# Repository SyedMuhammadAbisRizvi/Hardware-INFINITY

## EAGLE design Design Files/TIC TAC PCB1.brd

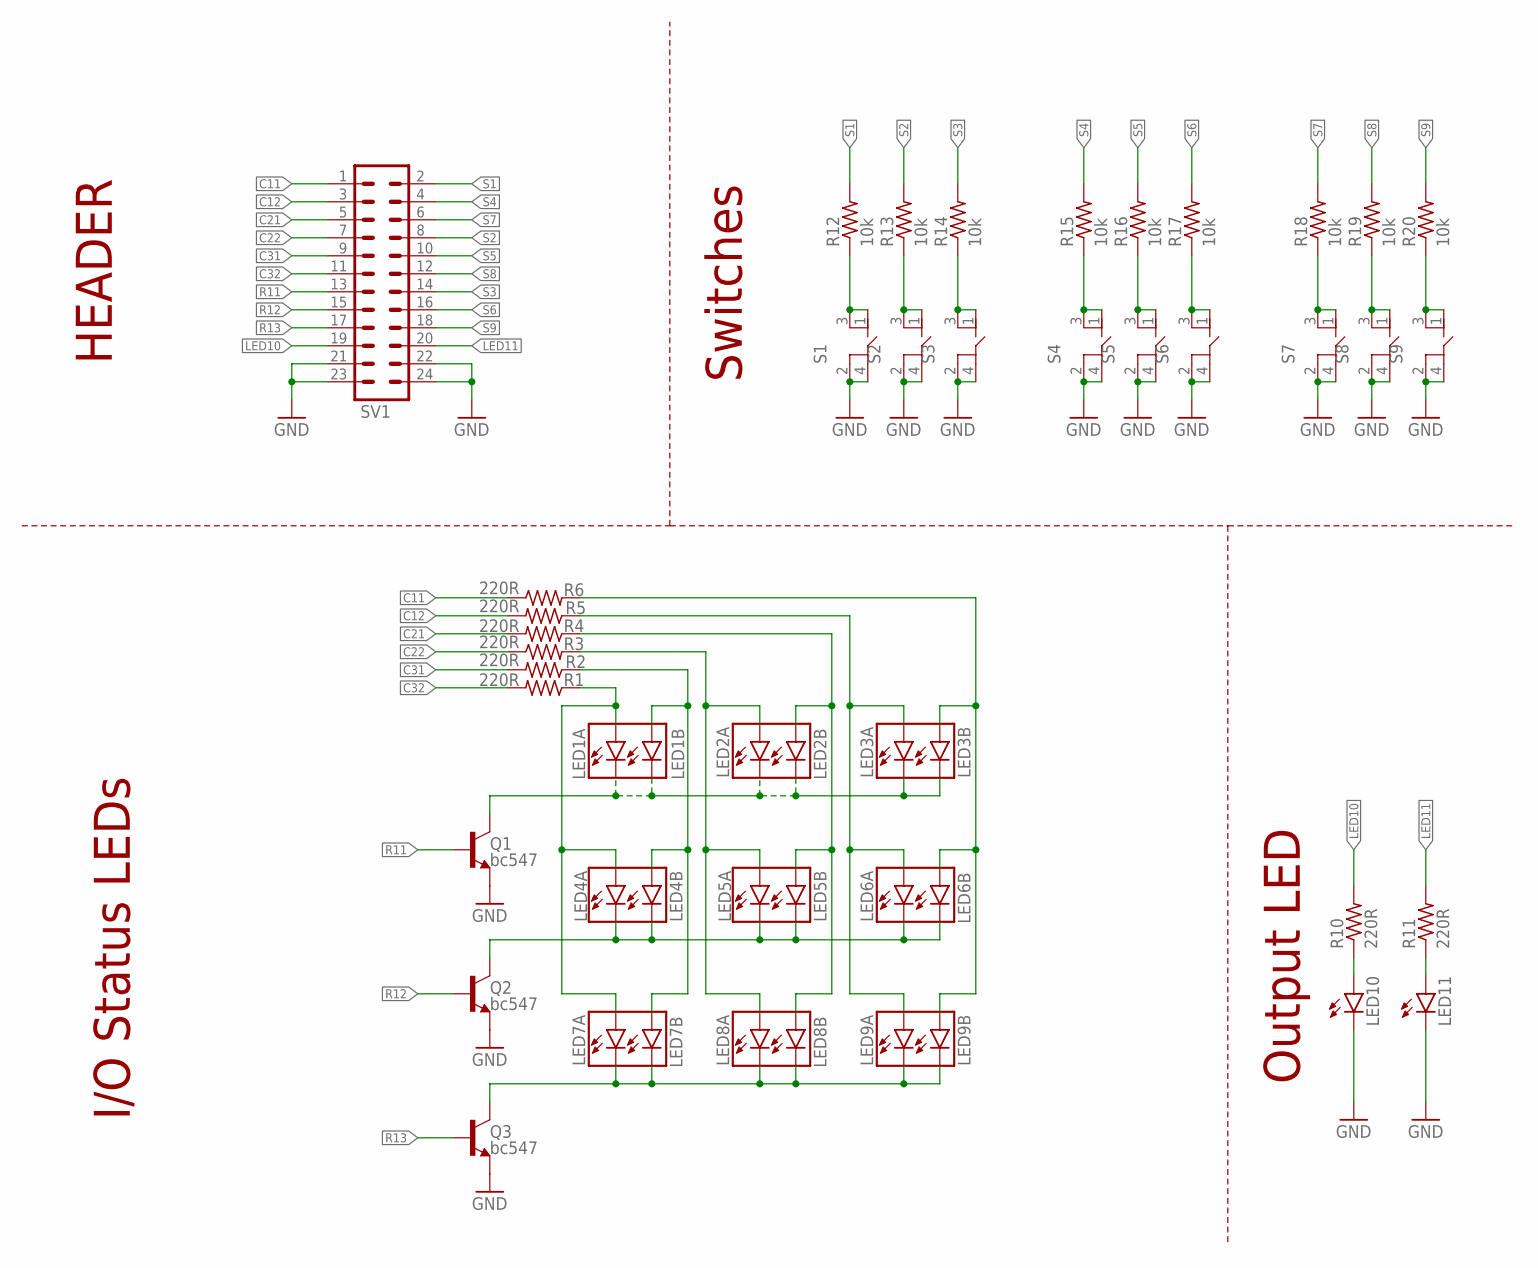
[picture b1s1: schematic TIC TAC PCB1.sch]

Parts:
LED1A, LED1B, LED2A, LED2B, LED3A, LED3B, LED4A, LED4B, LED5A, LED5B, LED6A, LED6B, LED7A, LED7B, LED8A, LED8B, LED9A, LED9B: LEDSML0805; SML0805
LED10, LED11: LEDSMT1206; 1206
Q1, Q2, Q3: bc547; SOT23-3
R1, R2, R3, R4, R5, R6, R10, R11: 220R; M0805
R12, R13, R14, R15, R16, R17, R18, R19, R20: 10k; M0805
S1, S2, S3, S4, S5, S6, S7, S8, S9: TS04-66-95-BK-100-SMT; SW_TS04-66-95-BK-100-SMT
SV1: MA12-2

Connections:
C11: R6.1, SV1.1
C12: R5.2, SV1.3
C21: R4.2, SV1.5
C22: R3.1, SV1.7
C31: R2.2, SV1.9
C32: R1.2, SV1.11
GND: LED10.C, LED11.C, Q1.2 (E), Q2.2 (E), Q3.2 (E), S1.2 (3), S1.4, S2.2 (3), S2.4, S3.2 (3), S3.4, S4.2 (3), S4.4, S5.2 (3), S5.4, S6.2 (3), S6.4, S7.2 (3), S7.4, S8.2 (3), S8.4, S9.2 (3), S9.4, SV1.21, SV1.22, SV1.23, SV1.24
LED10: R10.2, SV1.19
LED11: R11.2, SV1.20
unnamed: LED1B.A, LED4B.A, LED7B.A, R2.1
unnamed: R12.1, S1.1, S1.3 (2)
unnamed: R13.1, S2.1, S2.3 (2)
unnamed: R14.1, S3.1, S3.3 (2)
unnamed: R15.1, S4.1, S4.3 (2)
unnamed: R16.1, S5.1, S5.3 (2)
unnamed: R17.1, S6.1, S6.3 (2)
unnamed: R18.1, S7.1, S7.3 (2)
unnamed: R19.1, S8.1, S8.3 (2)
unnamed: R20.1, S9.1, S9.3 (2)
unnamed: LED2B.A, LED5B.A, LED8B.A, R4.1
unnamed: LED3B.A, LED6B.A, LED9B.A, R6.2
unnamed: LED2A.A, LED5A.A, LED8A.A, R3.2
unnamed: LED3A.A, LED6A.A, LED9A.A, R5.1
unnamed: LED1A.A, LED4A.A, LED7A.A, R1.1
unnamed: LED10.A, R10.1
unnamed: LED11.A, R11.1
unnamed: LED1A.C, LED1B.C, LED2A.C, LED2B.C, LED3A.C, LED3B.C, Q1.3 (C)
unnamed: LED4A.C, LED4B.C, LED5A.C, LED5B.C, LED6A.C, LED6B.C, Q2.3 (C)
unnamed: LED7A.C, LED7B.C, LED8A.C, LED8B.C, LED9A.C, LED9B.C, Q3.3 (C)
R11: Q1.1 (B), SV1.13
R12: Q2.1 (B), SV1.15
R13: Q3.1 (B), SV1.17
S1: R12.2, SV1.2
S2: R13.2, SV1.8
S3: R14.2, SV1.14
S4: R15.2, SV1.4
S5: R16.2, SV1.10
S6: R17.2, SV1.16
S7: R18.2, SV1.6
S8: R19.2, SV1.12
S9: R20.2, SV1.18

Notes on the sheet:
HEADER
I/O Status LEDs
Switches
Output LED

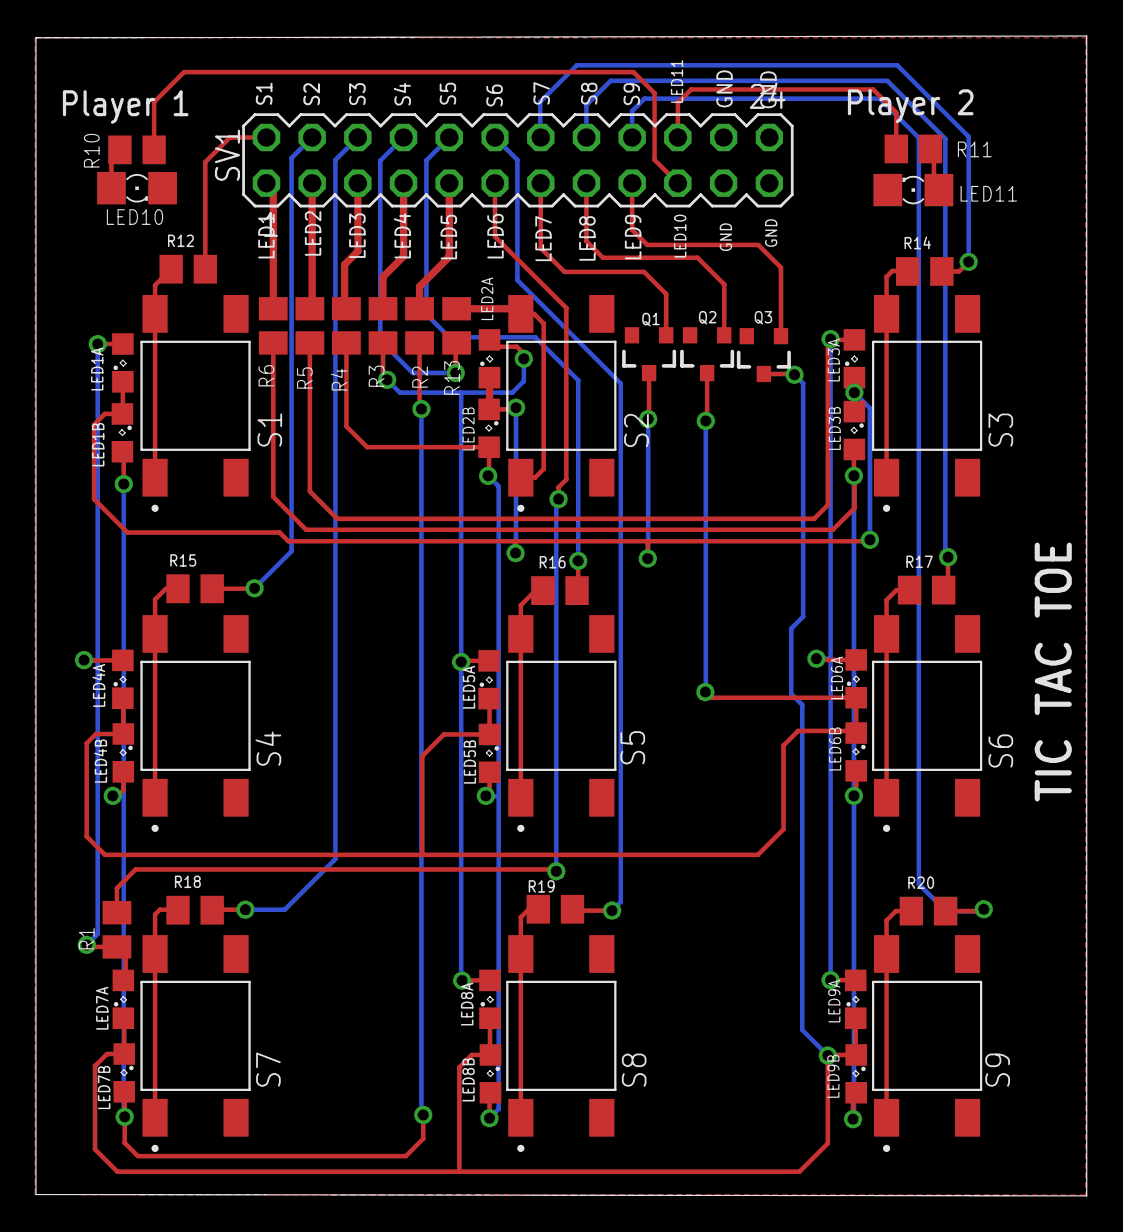
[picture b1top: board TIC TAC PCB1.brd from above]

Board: 2 copper layers, 58.4 x 64.4 mm, 50 parts (0 on the bottom side), 41 nets.

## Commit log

2022-06-24 Create VHDL
2022-06-24 Create TestBench
2022-07-06 Create Exe3_by_pritish
2022-07-06 Add files via upload
    Exercise 3 solved by pritish

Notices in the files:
parts and their libraries:
SparkFun-DiscreteSemi: Licensing: Creative Commons ShareAlike 4.0 International - https://creativecommons.org/licenses/by-sa/4.0
